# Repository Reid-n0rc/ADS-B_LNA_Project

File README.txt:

The filter/LNA project is designed to improve the ADS-B Reception of a RTL-SDR USB Dongle.  More on operation of the dongle and reception of ADS-B can be found at <http://www.reddit.com/r/rtlsdr>.

There are three elements extrenal to the software/sdr that this project emcompasses: the antenna, frontend filter, and LNA.  

ANTENNA:
----------
Any antenna that covers 1090MHz can be used for this purpose.  I am using a design found here: <http://www.sprut.de/electronic/pic/projekte/adsb/adsb_en.html#antenne>.

FILTER:
----------
Files for the filter design are contained the in the Filter directory.  There are two versions of the filter layout.  The "standard" filter, and filter_slant.  Filter_slant is the same as filter, just adjusted so the connectors are in a line in the X/Y Plane.  This will allows for a narrower PCB, and keeps any forces in the same direction, ie. doesn't try to pull the connector off to the side.  This is good for an antenna mounted design.

The main filter directory contains the .dxf files for the filter design.  You can use a free dxf viewer to see the filter and print it.  be sure that if you print the file to etch a filter, that it is 1:1 scale, otherwise the frequency of operation will be shifted.

Eagle specific files are contained in the eagle specific sub-directory.  The script (.scr) files can be used to generate the filter in any board layout.

If you're sending out the PCB for fab, make sure there is no solder mask over the PCB area, as this can affect the filter's frequency response.  You can take the .brd files and send them directly to OSH Park <http://oshpark.com/> for fabrication.

Filter performance can be seen in the Test_Data sub-directory.

LNA:
----------
The LNA design is still in the works, but is based on the design shown here: <http://www.lll.lu/~edward/edward/adsb/preamp/ADSBpremap.html> and modified as per the instructions of Dr. Ken Filardo, KA0THK

CC-BY-SA N0RC, 2013.

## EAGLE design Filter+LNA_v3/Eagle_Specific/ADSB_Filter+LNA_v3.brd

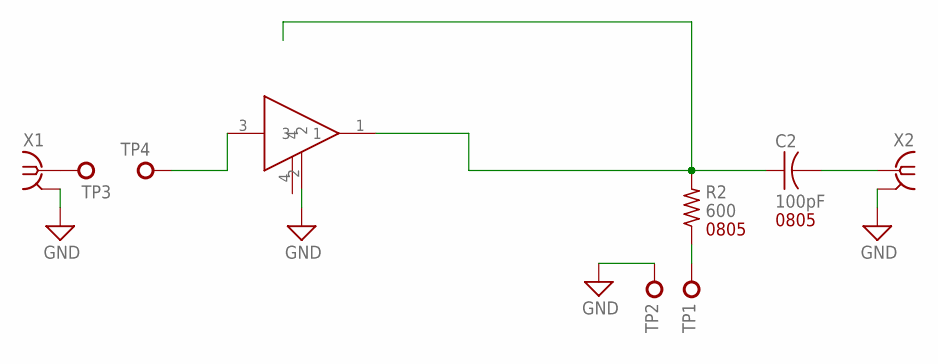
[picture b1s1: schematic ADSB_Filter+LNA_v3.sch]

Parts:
C2: 100pF; 0805
R2: 600; 0805
TP1, TP2: TEST_POINTS76_150; SMD_76_150
TP3, TP4: TEST_POINTS8_8; SMD_8_8
U$1: SPF-5043Z; SOT-343_2&4_FUSED
X1, X2: SMA-142-0701-801/806; J502-ND-142-0701-801/806

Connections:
1: TP3.1, X1.1
10: TP4.1, U$1.3
GND: TP2.1, U$1.2, X1.G@1 (GND), X1.G@2 (GND), X1.G@3 (GND), X1.G@4 (GND), X2.G@1 (GND), X2.G@2 (GND), X2.G@3 (GND), X2.G@4 (GND)
unnamed: C2.1, R2.2, U$1.1
unnamed: R2.1, TP1.1
unnamed: C2.2, X2.1

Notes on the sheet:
0805

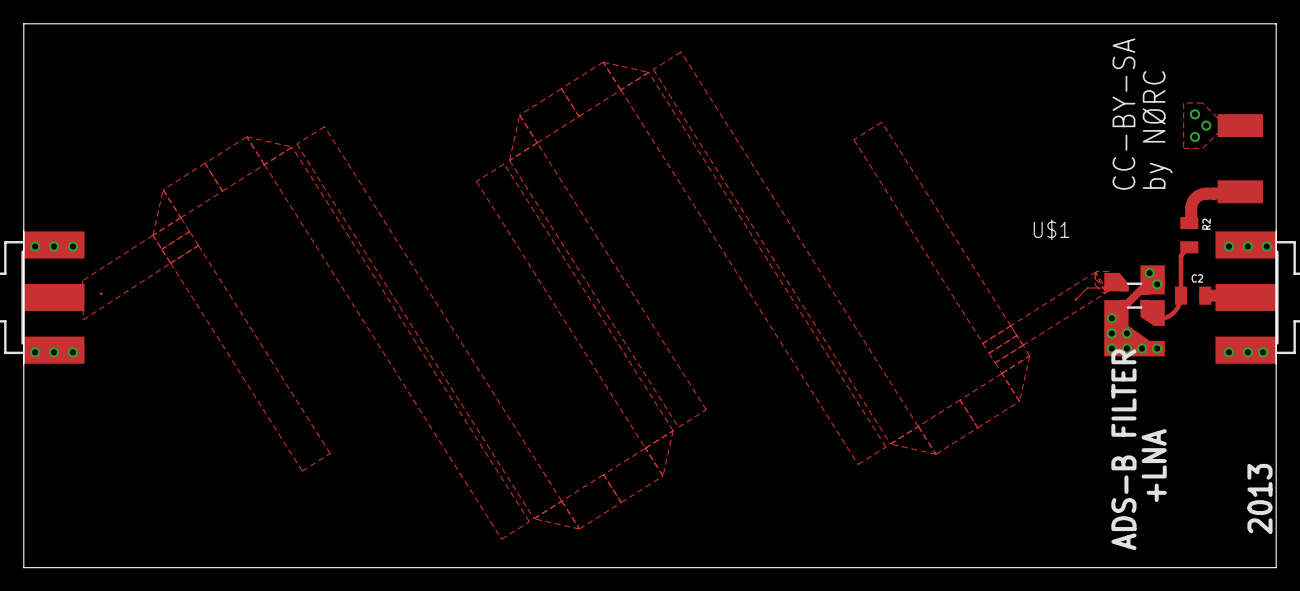
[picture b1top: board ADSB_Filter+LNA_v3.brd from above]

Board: 2 copper layers, 105.3 x 45.7 mm, 9 parts (0 on the bottom side), 6 nets.

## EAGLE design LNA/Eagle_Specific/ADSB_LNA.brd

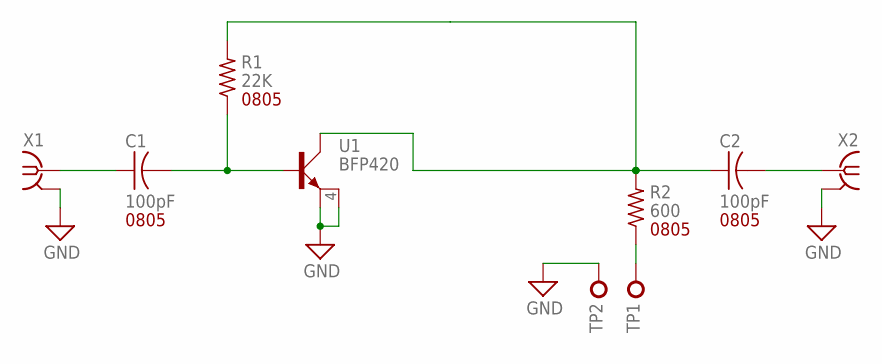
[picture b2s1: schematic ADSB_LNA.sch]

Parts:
C1, C2: 100pF; 0805
R1: 22K; 0805
R2: 600; 0805
TP1, TP2: TEST_POINTS76_150; SMD_76_150
U1: BFP420; SOT343_INFINEON
X1, X2: SMA-142-0701-801/806; J502-ND-142-0701-801/806

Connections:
GND: TP2.1, U1.2 (E1), U1.4 (E2), X1.G@1 (GND), X1.G@2 (GND), X1.G@3 (GND), X1.G@4 (GND), X2.G@1 (GND), X2.G@2 (GND), X2.G@3 (GND), X2.G@4 (GND)
unnamed: C1.1, X1.1
unnamed: C1.2, R1.1, U1.1 (B)
unnamed: C2.1, R1.2, R2.2, U1.3 (C)
unnamed: R2.1, TP1.1
unnamed: C2.2, X2.1

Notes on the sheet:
0805

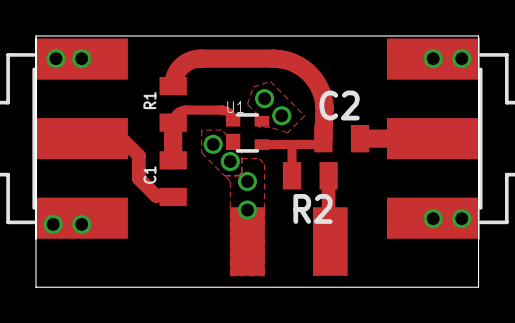
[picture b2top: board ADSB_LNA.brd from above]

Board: 2 copper layers, 24.6 x 14.0 mm, 9 parts (0 on the bottom side), 6 nets.

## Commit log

2013-04-15 Initial commit of filter design
2013-04-15 Reorganized dir, added .dxf files, test data
2013-04-15 Added Genesys Designs
2013-05-06 Added files on the Amp alone
2013-05-06 Added test data
2013-05-07 Added Filter+LNA PCB
2013-05-07 Updated Layout
2013-05-07 Changed file names and added Layouts as PDFs
    Changed file names to better describe what what is in them. Added
    layout as B&W PDF files with dimensions to allow for etching PCB with
    toner transfer or other process.
2013-05-07 Updated .gitignore to ignore Eagle backup files
    Ignores any .s## .b## or .l##
2013-05-07 Moved Filter&LNA Layout PDFs to their own folder
2013-05-07 Change width of copper pour from 0 to 1
    Copper pour with width 0 times out the OSH Park service. Changed to 1
    as per @laen
2013-05-07 Minor changes to Filter+LNA Layout
2013-05-07 Added license info to all layouts
2013-05-07 Added BOM for LNA. Importable into Digi-Key
2013-05-07 Updated Filter+LNA gerber. Removed old filename.
2013-05-13 README for Gerber Extensions
    Added README for each Gerber Files directory explaining what each file
    type corresponds to.
2013-05-13 Removed dimm from layouts
2013-05-13 replaced gerbers for ones formatted for ITEAD
2013-05-13 Added *.sch to be compatible with Upverter
2013-05-13 Added Filter+LNA_v2 - Not finished
    Added Filter+LNA_v2. Schematic and layout hosted at Upverter:
    http://upverter.com/RTLSDR_Addons/fb2911b6e6312c93/Filter--LNA-ver-2/
    Gerbers here are not finished.
2013-09-14 Finished Layout with SPF5043Z
